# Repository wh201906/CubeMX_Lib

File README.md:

# CubeMX_Lib
Some snippets for my STM32F4/H7 board  
封装了一些常用代码，仅针对手上的两款主力开发板(F407VE/H750VB)进行编写及测试  
Module文件夹内为可复用的功能模块，Project文件夹内为CubeMX+HAL库编写的项目  

*** 

使用方法：  
1.新建项目文件夹，并从Template文件夹中拷入对应.ioc文件  
2.重命名.ioc文件，打开，配置工程  
3.生成工程后配置编译器版本为6  
4.include目录添加../../../Module  
5.双击Project窗口，配置所需模块  

***

工程中提示无法找到HAL库相关函数时检查.ioc文件中软件包的配置情况(选择使用最新版本软件包)

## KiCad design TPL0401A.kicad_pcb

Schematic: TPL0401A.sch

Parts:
C1: C; C_0805_2012Metric
J1, J2: Conn_01x04_Male; PinHeader_1x04_P2.54mm_Vertical
R1, R2: R; R_0805_2012Metric
U1: TPL0401A-10-Q1; Texas_R-PDSO-G6

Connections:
+5V: C1.1, J1.1, R1.1, R2.1, U1.1 (VDD)
GND: C1.2, J1.2, U1.2 (GND)
unnamed: J2.1, J2.2, U1.6 (H)
unnamed: J2.3, J2.4, U1.5 (W)
SCL: J1.3, R1.2, U1.3 (SCL)
SDA: J1.4, R2.2, U1.4 (SDA)

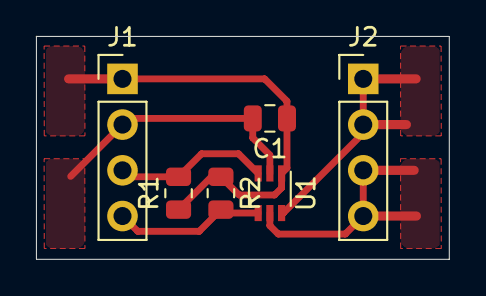
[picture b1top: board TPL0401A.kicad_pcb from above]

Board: 2 copper layers, 22.9 x 12.4 mm, 6 parts (0 on the bottom side), 6 nets.

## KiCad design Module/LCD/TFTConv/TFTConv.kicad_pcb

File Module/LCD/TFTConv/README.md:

WARNING: This PCB doesn't support all black boards!

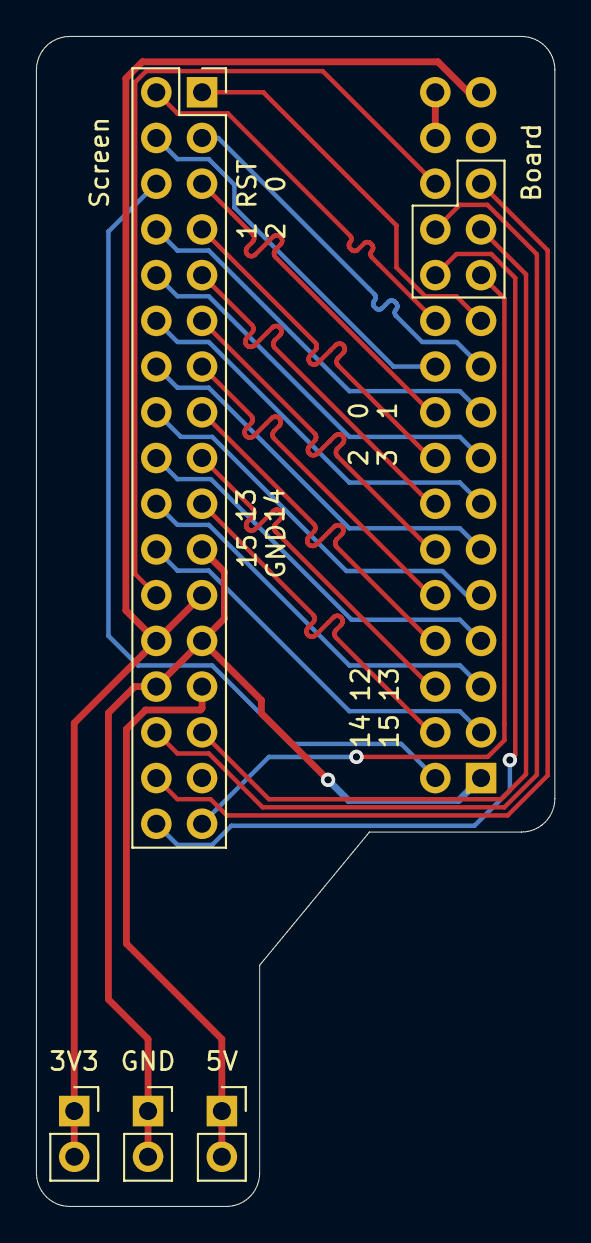
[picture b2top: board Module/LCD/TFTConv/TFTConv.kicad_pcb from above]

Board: 2 copper layers, 28.8 x 65.0 mm, 5 parts (1 on the bottom side), 31 nets.

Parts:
3V3, 5V: Conn_01x02_Female; PinSocket_1x02_P2.54mm_Vertical
Board: Board; PinSocket_2x16_P2.54mm_Vertical
GND: Conn_01x02_Female; PinSocket_1x02_P2.54mm_Vertical
Screen: Screen; PinSocket_2x17_P2.54mm_Vertical

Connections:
+3V3: 3V3.1, 3V3.2, Board.31, Screen.23, Screen.26
+5V: 5V.1, 5V.2, Screen.27
/FSMC_Ax: Board.21, Screen.1
/FSMC_D0: Board.18, Screen.5
/FSMC_D1: Board.17, Screen.8
/FSMC_D2: Board.16, Screen.7
/FSMC_D3: Board.15, Screen.10
/FSMC_D4: Board.14, Screen.9
/FSMC_D5: Board.13, Screen.12
/FSMC_D6: Board.12, Screen.11
/FSMC_D7: Board.11, Screen.14
/FSMC_D8: Board.10, Screen.13
/FSMC_D9: Board.9, Screen.16
/FSMC_D10: Board.8, Screen.15
/FSMC_D11: Board.7, Screen.18
/FSMC_D12: Board.6, Screen.17
/FSMC_D13: Board.5, Screen.20
/FSMC_D14: Board.4, Screen.19
/FSMC_D15: Board.3, Screen.22
/FSMC_NEx: Board.22, Screen.2
/FSMC_NOE: Board.19, Screen.3
/FSMC_NWE: Board.20, Screen.4
/LCD_BL: Board.28, Screen.24
/RST: Board.2, Screen.6
/T_CS: Board.24, Screen.34
/T_MISO: Board.26, Screen.30
/T_MOSI: Board.25, Screen.29
/T_PEN: Board.27, Screen.32
/T_SCK: Board.23, Screen.33
GND: Board.1, GND.1, GND.2, Screen.21, Screen.25, Screen.28
GND2: Board.30, Board.32

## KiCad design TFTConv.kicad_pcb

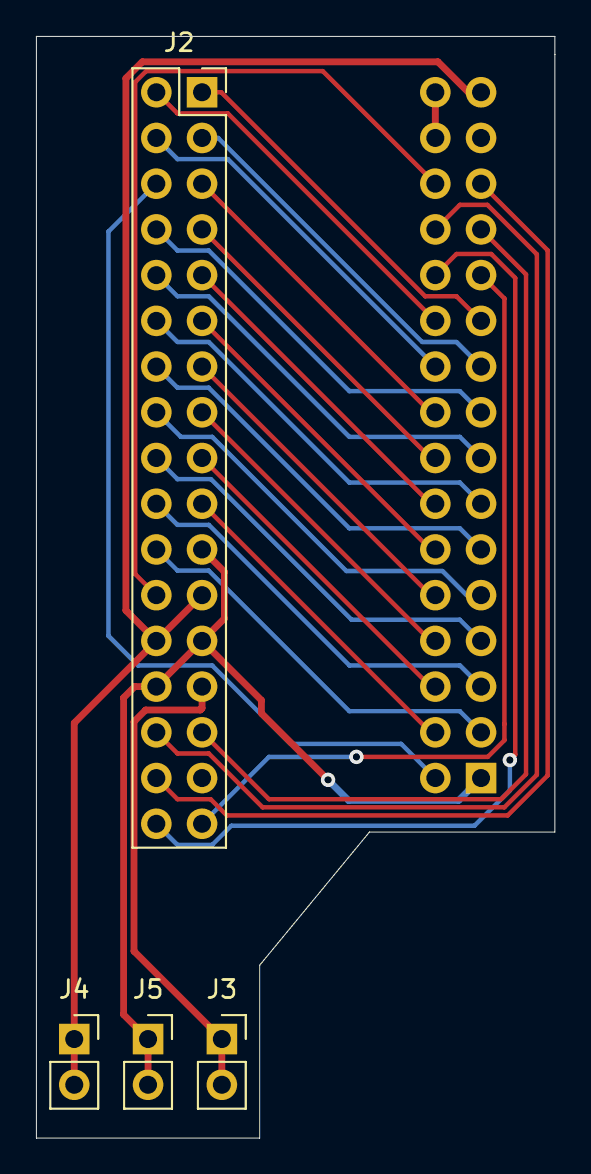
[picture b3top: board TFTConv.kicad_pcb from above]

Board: 2 copper layers, 28.8 x 61.2 mm, 5 parts (1 on the bottom side), 31 nets.

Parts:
J1: Board; PinSocket_2x16_P2.54mm_Vertical
J2: Screen; PinSocket_2x17_P2.54mm_Vertical
J3, J4, J5: Conn_01x02_Female; PinSocket_1x02_P2.54mm_Vertical

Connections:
+3V3: J1.31, J2.23, J2.26, J4.1, J4.2
+5V: J2.27, J3.1, J3.2
/FSMC_Ax: J1.21, J2.1
/FSMC_D0: J1.18, J2.5
/FSMC_D1: J1.17, J2.8
/FSMC_D2: J1.16, J2.7
/FSMC_D3: J1.15, J2.10
/FSMC_D4: J1.14, J2.9
/FSMC_D5: J1.13, J2.12
/FSMC_D6: J1.12, J2.11
/FSMC_D7: J1.11, J2.14
/FSMC_D8: J1.10, J2.13
/FSMC_D9: J1.9, J2.16
/FSMC_D10: J1.8, J2.15
/FSMC_D11: J1.7, J2.18
/FSMC_D12: J1.6, J2.17
/FSMC_D13: J1.5, J2.20
/FSMC_D14: J1.4, J2.19
/FSMC_D15: J1.3, J2.22
/FSMC_NEx: J1.22, J2.2
/FSMC_NOE: J1.19, J2.3
/FSMC_NWE: J1.20, J2.4
/LCD_BL: J1.28, J2.24
/RST: J1.2, J2.6
/T_CS: J1.24, J2.34
/T_MISO: J1.26, J2.30
/T_MOSI: J1.25, J2.29
/T_PEN: J1.27, J2.32
/T_SCK: J1.23, J2.33
GND: J1.1, J2.21, J2.25, J2.28, J5.1, J5.2
GND2: J1.30, J1.32

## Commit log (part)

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2021-01-25 Beep: Add Bad Apple Demo
2021-01-26 USART: Update F4 project
2021-01-27 SoftI2C: Finish transmit logic for one byte
2021-01-28 SoftI2C: Add support for 10bit addr. Change ACK and NACK
2021-01-29 OLED&SoftI2C: works fine
2021-01-29 OLED: Update projects
2021-01-30 MLX90614: Can receive ACK from slave device now
    1.Open-Drain can be used with pull up on STM32F4.
    2.In I2C, use Open-Drain rather than Push-Pull, they have different waveforms at posedge(and different hardware struct).
    3.GPIO speed can be configured at a low value to filter some spikes.
    4.This commit has some bugs, and the timing sequences need to be checked.
    5.Using repeat START doesn't mean send STOP.
2021-01-30 MLX90614: Changing timing sequence, no affect
2021-01-31 MLX90614&SoftI2C: Support PEC when read RAM
2021-01-31 Update dependency
2021-02-01 VL53L0X: Try to migrate, build passed
    vl53l0x_i2c_platform.h: Remve unused functions
    vl53l0x_i2c_comms.c: Implement I2C communication by my I2C Module and remove unused functions
    vl53l0x_platform_log.h: Disable log function
    vl53l0x_platform_log.c: Disable log function, remove Windows related functions
    vl53l0x_platform.c: Remove header file of Windows
    vl53l0x_types.h: Undefine existing types
2021-02-03 ArduinoComm: UART version, up to 2Mbit/s, Tx/Rx test passed
2021-02-05 FFT: Add module
2021-02-06 FFT: Add spectrum analyzer demo
2021-02-09 AD9280: USE PWM as clk
2021-02-11 AD9280: Prototype test passed
    GPIO is on AHB1, which cannot be accessed by DMA1 in STM32F4
2021-02-25 RMS: Add a simple project
2021-02-27 FFT: Handle response from UART Screen
    This will reduce data error when transmit waveform data
2021-03-01 FFT: Try arm_rfft_q15(), not fully implemented
2021-03-06 OLED: Remove stdio.h and string.h
2021-03-06 FFT: Toggle PE4 for speed test
2021-03-08 FFT: Discard q15 version
    According to the official test result, the arm_rfft_q15() doesn't have
    a significant performance increasement than arm_rfft_fast_f32() when
    using FPU and -O3 optimization.
    And, the fix point real number will sacrifice much precision than float
    point real number. This is particularly obvious when doing a FFT, whose
    output is upscaled a lot.
2021-03-19 ParaIO: Seperate from AD9280 partially
    It seems that the ParaIO_Start_In() in the main loop doesn't enable the DMA,
    so I need to put ParaIO_Init_DMA_In() in the main loop too.
2021-03-20 ParaIO: PWM is done, output test failed
2021-03-22 SPIFlash: Add project
2021-03-22 SPIFlash: Read/Write single byte(not tested)
2021-03-23 SPIFlash: Some modification
2021-03-25 SPIFlash: Full of bugs, debugging...
2021-03-26 WaveGen: Update firmware
2021-03-26 FIR: Double buffer enabled
2021-03-26 FIR: Quad buffer, buf0 and buf2 bypassed, no phase jump
    the buf0 will be write only once, the buf2 will be empty, the data is floating in buf1 and buf3
    need further analysis
2021-03-27 FIR: Low pass filter
    Bad performance with high pass filter
    Need to use quad buffer to prevent copy
    Need to test the performance
2021-03-29 SPIFlash: Bug fixed, not fully tested
    The Write Enable needs to be called before EVERY Page Program
2021-03-30 MLX90614: Update firmware
2021-03-31 OLED: Reduce function parameters
2021-04-02 OLED: Speed up
    for OLED_ShowStr() when strlen is 30:
    TEXTSIZE_SMALL:
    42.7ms->10.04ms(-76.5%)
    TEXTSIZE_BIG:
    104.2ms->26.0ms(-75.0%)
2021-04-03 VL53L0X: Migrating API
    Delete previous platform-specified files
    Disable log funcions
    Clean up including files
2021-04-03 VL53L0X: Migrating API
    vl53l0x_platform.c: Implement PollingDelay(), ReadMulti(), RdByte(), WriteMulti() and WrByte(), Clean up
    vl53l0x_platform_log.c: Disable trace_print_module_function() and VL53L0X_trace_config()
    vl53l0x_types.h: Include main.h to support pre-defined types
    vl53l0x_platform.h: Add VL53L0X_MAX_STRING_LENGTH_PLT for debug_string[](useless though), Clean up
    Fix including path for all files(from xxx.h to ../inc/xxx.h)
2021-04-04 SoftI2C: Fix a bug
    When the master device finishes reading, it should send NACK before STOP in order to tell slave device to release the bus.
    VL53L0X init passed
2021-04-05 Timer: more precise version
2021-04-07 GPIO: Add project(F103C8)
    A little demo for UART and GPIO
2021-04-08 Freq_L: module test passed(with CubeMX configuration)
2021-04-09 Freq_L: Add overflow detect, minimum 5Hz (Bugs finded in myftoa())
2021-04-10 UART: Add L431 support
2021-04-11 Freq_L: minimum 0.1Hz(less precise when frequency is high)
2021-04-12 Freq_H: Prototype test passed
    The PWM mode, CH polarity and pulse need to be modified
2021-04-14 Add ports
2021-04-16 Freq_H: module test passed(with CubeMX configuration)
2021-04-16 Freq_H: finish
2021-04-24 SoftI2C: Speed up, fast mode plus test passed
    Tested with AT24C04D I2C EEPROM @943.4kHz
    the (ticks/4) will be less precise than (ticks/2), and introduce more instructions
    the actural clock speed is not the same as the expected clock speed
    Tested with F407VE, ArmClang V6.15, -O3
    100k->99.03k
    400k->318.5k
2021-04-25 OS_LED: Migrate to ArmCompiler 6
    Use FreeRTOS/Source/portable/GCC rather than FreeRTOS/Source/portable/RVDS,
    because ARM Compiler 6 only supports GNU style inline assembler statements.
2021-05-07 VL53L0X: Add F103 project
2021-05-08 README: Typo
2021-05-08 FFT: Use UART2 for display
2021-05-09 WavPlayer: PCM5102A works
    The connction betwween FMT pin and GND is not stable.
    Then I spent the whole day to figure it out.
    =_=
2021-05-11 TFTConv: Gerber out
2021-05-14 VL53L1X: Add API
    API is from STSW-IMG009, the ultra light driver. Nothing modified.
2021-05-14 VL6180X: Add API
    API is from STSW-IMG003. Nothing modified.
2021-05-15 WaveGen: Init HMI project
2021-05-15 Revert "WaveGen: 8bit mode, failed"
    This reverts commit 65266585d33f8935d7841c74553e264465450aaa.
2021-05-15 WaveGen: HMI updated
2021-05-15 WaveGen: Freq part
    240M/arr/psc/(len)
2021-05-15 WaveGen: My screen boomed
2021-05-16 LCD: Add project
    The TFT-LCD screen is from ALIENTEK(正点原子).
    I copied the driver (lcd.c/lcd.h/font.h) from samples and do some migrations.
    The FSMC uses NE1, so the address is from 0x60000000 to 0x63FFFFFF.
    The connector on my board uses register A18(to PD13),
    so the base address start from 0x7FFFE
    (contains 18 '1' and a trailing '0', based on the given algorithm).
2021-05-19 SoftI2C: Unify user-level code
2021-05-20 Tof: Failed to use VL6180X
    The SDA is always low
2021-05-22 Tof: Misc
    All Tof module test passed.
    The VL6180X and VL53L1X use 16bit register address
    The VL53L1X uses 8bit register address
    Change Init() for I2C devices
2021-05-22 AD9833: SPI can be changed
    And update firmware
2021-05-23 Util: Optimize myftoa()
    Add rounding feature
    Add myftoa_FD() for fixed decimal digits
2021-05-28 SoftI2C: Search available I2C devices
2021-05-29 Oscilloscope: Ugly and useless
    TODO:
    Show waveform after a certain delay
    Change trigger condition
2021-06-01 AD7190: Read and write
2021-06-01 AD7190: Some getter and setter
2021-06-02 Oscilloscope: More display mode
    Support dot/vector display
    TODO:
    The dot display seems to cost much fewer time than vector display,
    which has a better appearance.
    I might do the calculation before showing the whole waveform for better result
2021-06-03 EC11: Demo for EC11 encoder
    The bare EC11 encoder is easy to make jitters.
    I solder 3 capacitors(33nF) for A/B phase and the key
2021-06-05 AD9834: Add project
    Got a bug when sending a fraction by UART
2021-06-12 ADS1115: Init
2021-06-18 Freq_H: delta=100Hz, T_meas=10ms
2021-06-18 Freq: Auto range(untested)
2021-06-19 Freq: Finished
2021-06-25 TPL0401A: Pull up SCL and SDA in PCB
2021-06-29 TPL0401: Finished
    The board is not designed very well, so the speed cannot reach 400k
2021-07-01 FFT: Optimize display
    Change baudrate from 115200 to 512000(4x faster)
    Refresh the whole page at once to reduce flickering
2021-07-04 Servo: First try
    the pulse need to be changed gradually, otherwise the current can be horrible
2021-07-05 Servo: TIM10 Test passed
    The TIM10 has one pulse mode, even the register map doesn't have OPM bit.
2021-07-05 THD: Add function in myfft.c
    Hanning Window works fine, I might need a Flattop window
2021-07-06 THD: Window configuration by UART
2021-07-07 PWMMeasure: Finished
2021-07-08 UART_LL: Finished
    Use circular queue
    Untested
2021-07-10 AD7190: Migrate to UART_LL
2021-07-12 THD: Channel selection in THD page
2021-07-12 THD: Fix some bugs
    The addt command will give responce twice,
    so the MCU should handle them both.
    The type of window in spectrum page should be updated
2021-07-13 THD:Optimize
    Remember to change MYFFT_LENGTH in main.h and myfft.h
    Use 3 stages of algothm to get average THD
    Stage1: direct average
    Stage2: moving average
    Stage3: change detect
2021-07-13 THD: Fix a bug
2021-07-13 THD: Pre-configured analog watch dog
    Need to check the interrupt(I only need the analog watch dog interrupt)
2021-07-14 ADF4351: Demo
    ADF4351 driver from KangWei Tech(康威电子)
2021-07-14 ADF4351: A small fix
    MyUART_ReadUntilWithEnd() behaves similar to MyUSARTx_ReadUntil()
2021-07-17 Spectrum: Use new ADF4351 driver
2021-07-20 Spectrum: Misc
2021-07-20 PE4302: Init
    Code from my senior
2021-07-21 Spectrum: compensate
2021-07-25 Misc
    Change GPIO of AD9910
    Add SPI Test project
    Add splitparam() in util.c
    Add ReadUntilWithZero() in myuart.c
2021-07-25 SPITest: Use LL driver
    It's my fault rather than a bug in LL driver
    The SPI hardware might be implemented with pipeline, so check BUSY bit is necessary
    Using LL driver will increase the speed, so the SignalTap can acquire the whole process
2021-07-28 AD9910_USB: Finished
2021-07-29 Si4463: Migrate to F407 with HAL driver
2021-07-30 Si4463: Tx test passed
    Add 433M support
    If the Si4463 doesn't work, the Init() will call itself recursively then lead to a HardFault(INVPC)
    The SDN doesn't work
2021-08-01 DAC8563: Speed up
    -O0, -O1, -O2, -O3 test passed(ArmClang, v6.15)
    time measured in us
    Optimize | SetA | SetB | SetBoth
    -O0| 18.45| 18.43| 35.92
    -O1| 8.99| 9.04| 17.46
    -O2| 8.90| 8.91| 17.11
2021-08-03 AD7606: BUSY is always LOW
2021-08-06 MPU: I2C communication
2021-08-07 MPU: DMP works
2021-08-11 Si4463: SDN works
    more waittime for CTS
2021-08-19 nRF24L01P: max 6 bytes
2021-08-19 Si4463: Clean up
2021-08-20 Si4463: Interrupt based receive
    Clear Rx interrupt AFTER reading FIFO
    After receive, set status to RX_TUNE then RX to receive next packet
2021-08-21 RDA5820: Read ID
    Add a code snippet file
2021-08-22 Si4703: Read ID
    Strange control interface
2021-08-23 Si4703: Demo
2021-08-24 nRF24L01P: Refactor IRQ code
2021-09-06 RDA5820: Band 76~108 doesn't work
2021-09-06 RemoteSniffer: A small demo
2021-09-07 RemoteSniffer: Refactor
    Use different bit order for halfByte(latest received bit in LSB)
    New trigger logic
    do alignment after acquire(makes deadzone)
2021-09-08 RemoteSniffer: timer is not necessary in async direct Tx mode
2021-09-10 PAJ7620: 8 gesture
    IDK how to make a wave gesture
2021-09-11 WaveTransfer: Latency test
    REMEMBER TO PULL UP RX PIN!!!
    In this spectial project(.uvprojx file > 1), use "rebuild" rather than "build"
    Update AD9280 project(sample on posedge, data change after 25ns)
2021-09-13 WaveTransfer: debugging
    seems like updateTimes++ is not an atomic operation
2021-09-17 ParaIO: Check DMA transfer complete flag
2021-09-18 Sweep: Init
2021-10-07 Some useless work
    (´；ω；`)
2021-10-07 Sweep: Fixed
    The AD9226 is a pipelined ADC, which has a pipeline delay(7 cycles)
2021-10-09 Sweep: LCR measurement
    Binary search for 0.707 point
    Reduce search steps
    Fix the amplitude bug when switching from freq_max to freq_min
2021-10-10 Sweep: Network detect
2021-10-23 WS2812: Test
    Handle DMA manually
    Failed to write to TIM1->CCMR1 right after the DMA transmition completed(no effect)
    Delay is necessary
2021-10-24 WS2812: Finished
    Some boundary condition need to be modified if necessary
2021-10-28 ADF4002: Unlock detect
2021-10-31 RDA5820: Tx test
    Works from 55.7M~115M
    Fix a bug in setFreq(), band 76~108 works
2021-11-04 WS2812: Fix a bug
2021-11-05 Tx: Basic UI
    Rx: queue
2021-11-05 Tx: FSK Test
2021-11-05 Rx: Add driver of TM1637
    from https://github.com/rogerdahl/stm32-tm1637
    The GPIO must be Push-Pull for higher speed
2021-11-06 Rx: Another demod
    Read level with clock recovery
2021-11-06 Misc
    Backup Tx node on L071CB and F103C8
    num+5, 0000->0005(reversed phase detect)
    Add AD9834 on Tx node
    Change SPI2 pinout on Rx node
2021-11-07 Tx: any LO freq
2021-11-07 Tx: Backup
